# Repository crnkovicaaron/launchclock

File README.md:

# Rocket Launch Countdown Clock
A standalone digital countdown clock for rocket launches.
It displays countdown and mission elapsed time, is controlled entirely using a keypad, and requires no external computer or network.
It is built around an ATmega328P microcontroller, DS3231 real-time clock, and MAX7219-driven 7-segment and dot matrix displays.

## Features
- LED Displays: 7-segment for time and dot matrix for mode/status glyphs
- Fully keypad-driven UI
- Launch and current time/date setting (including launch date nudging)
- Countdown pausing
- Low-power sleep mode
- Display brightness control
- Configurable countdown time display format
- Error handling including invalid inputs and RTC power loss

## Hardware
Custom PCB designed in KiCad around an ATmega328P microcontroller.

Key components: 
- **MCU**: ATmega328P
- **RTC**: DS3231M with CR1220 battery backup
- **Displays**: MAX7219-driven dual 4-digit 7-segment (5641AS) and 8x8 dot matrix (1088AS)
- **Input**: 4x4 matrix keypad
- **Power**: 5V DC via 5.5x2.1mm barrel jack (or solder pads to enclosure-mounted barrel jack)
- **Communication**: I²C (RTC) and SPI (display drivers & ISP)
- **Assembly**: Hand soldered; uses both THD and SMD components
- **Enclosure**: Custom 3D printed FreeCAD enclosure is WIP

KiCad schematic and PCB files are under the 'hardware/' directory. Assorted photos can be found under the 'assets/' directory.

Status: Version 2 is completed and functional. Version 3 is WIP.

## Firmware
Written in Arduino C++ (AVR) for the ATmega328P (Arduino Uno).

The firmware implements a keypad-driven state machine that manages countdown/MET display, time/date setting, pause, brightness, sleep, and error handling.

Key elements:

- **Libraries**: RTClib (DS3231), Keypad, LedControl (MAX7219), EEPROM, plus AVR sleep/power utilities
- **Architecture**: Event-driven keypad handling and periodic 1-second time updates; use of mode flags for UI states
- **Displays**: Dual MAX7219 display control with PROGMEM bitmaps
- **Persistence**: Launch time/date stored in EEPROM
- **Power**: Full power-down sleep mode woken by keypad pin-change interrupt
- **Robustness**: Input validation, RTC power-loss detection, and dedicated error states

Source is a single sketch organized into functional blocks (display, input, timekeeping, power, UI modes). Programming is performed via the board's ISP header.

## Development History
### Initial Prototype
This Arduino breadboard prototype was an MVP with the singular goal of counting down to the Artemis II launch, with all work being completed entirely the day prior. It has the 7-segment displays wired directly to an Arduino Mega, uses a DS1307 RTC breakout board, and lacks any inputs.

### Revised Prototype
This revised prototype contains around a month of additions and improvements to the initial prototype. These include the addition of keypad inputs (out of frame), a dot matrix display, and corrected/improved display wiring. The vast majority of the time since the initial prototype was spent programming the firmware.

### Version 1 PCB
This custom 2-layer PCB mounts directly to an Arduino Mega using header pins, and the 7-segment displays mount to the board. With exception to the SMD resistors, there are essentially no changes to the circuit or its components between the revised prototype and the version 1 board. The main goal of this design was to become familiar with KiCad and PCB design.

### Version 2 PCB
The main goal of this version was to eliminate the Arduino and breakout boards by integrating all necessary functionality onto the board itself. This includes driving the 7-segment displays with a MAX7219 in the same manner as the dot matrix to allow the use of an MCU that is easier to solder by hand (instead of the ATmega2560 used on the Arduino Mega). The board is still 2-layers, programming is done via the ISP header, and numerous test points were integrated for troubleshooting and experimentation.

### Version 3 PCB (Work in Progress)
In this version, the barrel jack is superseded by a USB-C port with power and USB 2.0 data functionality. The MCU and display drivers use surface-mount packages in favor of through holes and most passive components are downsized to 0603 parts compared to the 1206 parts on version 2, allowing the total board area to be reduced by 28% compared to version 2. The board was designed to reduce EMI (mainly radiated), which includes switching to a 4-layer board. The revision also addresses numerous smaller issues with the version 2 board, including a soft but audible whine.

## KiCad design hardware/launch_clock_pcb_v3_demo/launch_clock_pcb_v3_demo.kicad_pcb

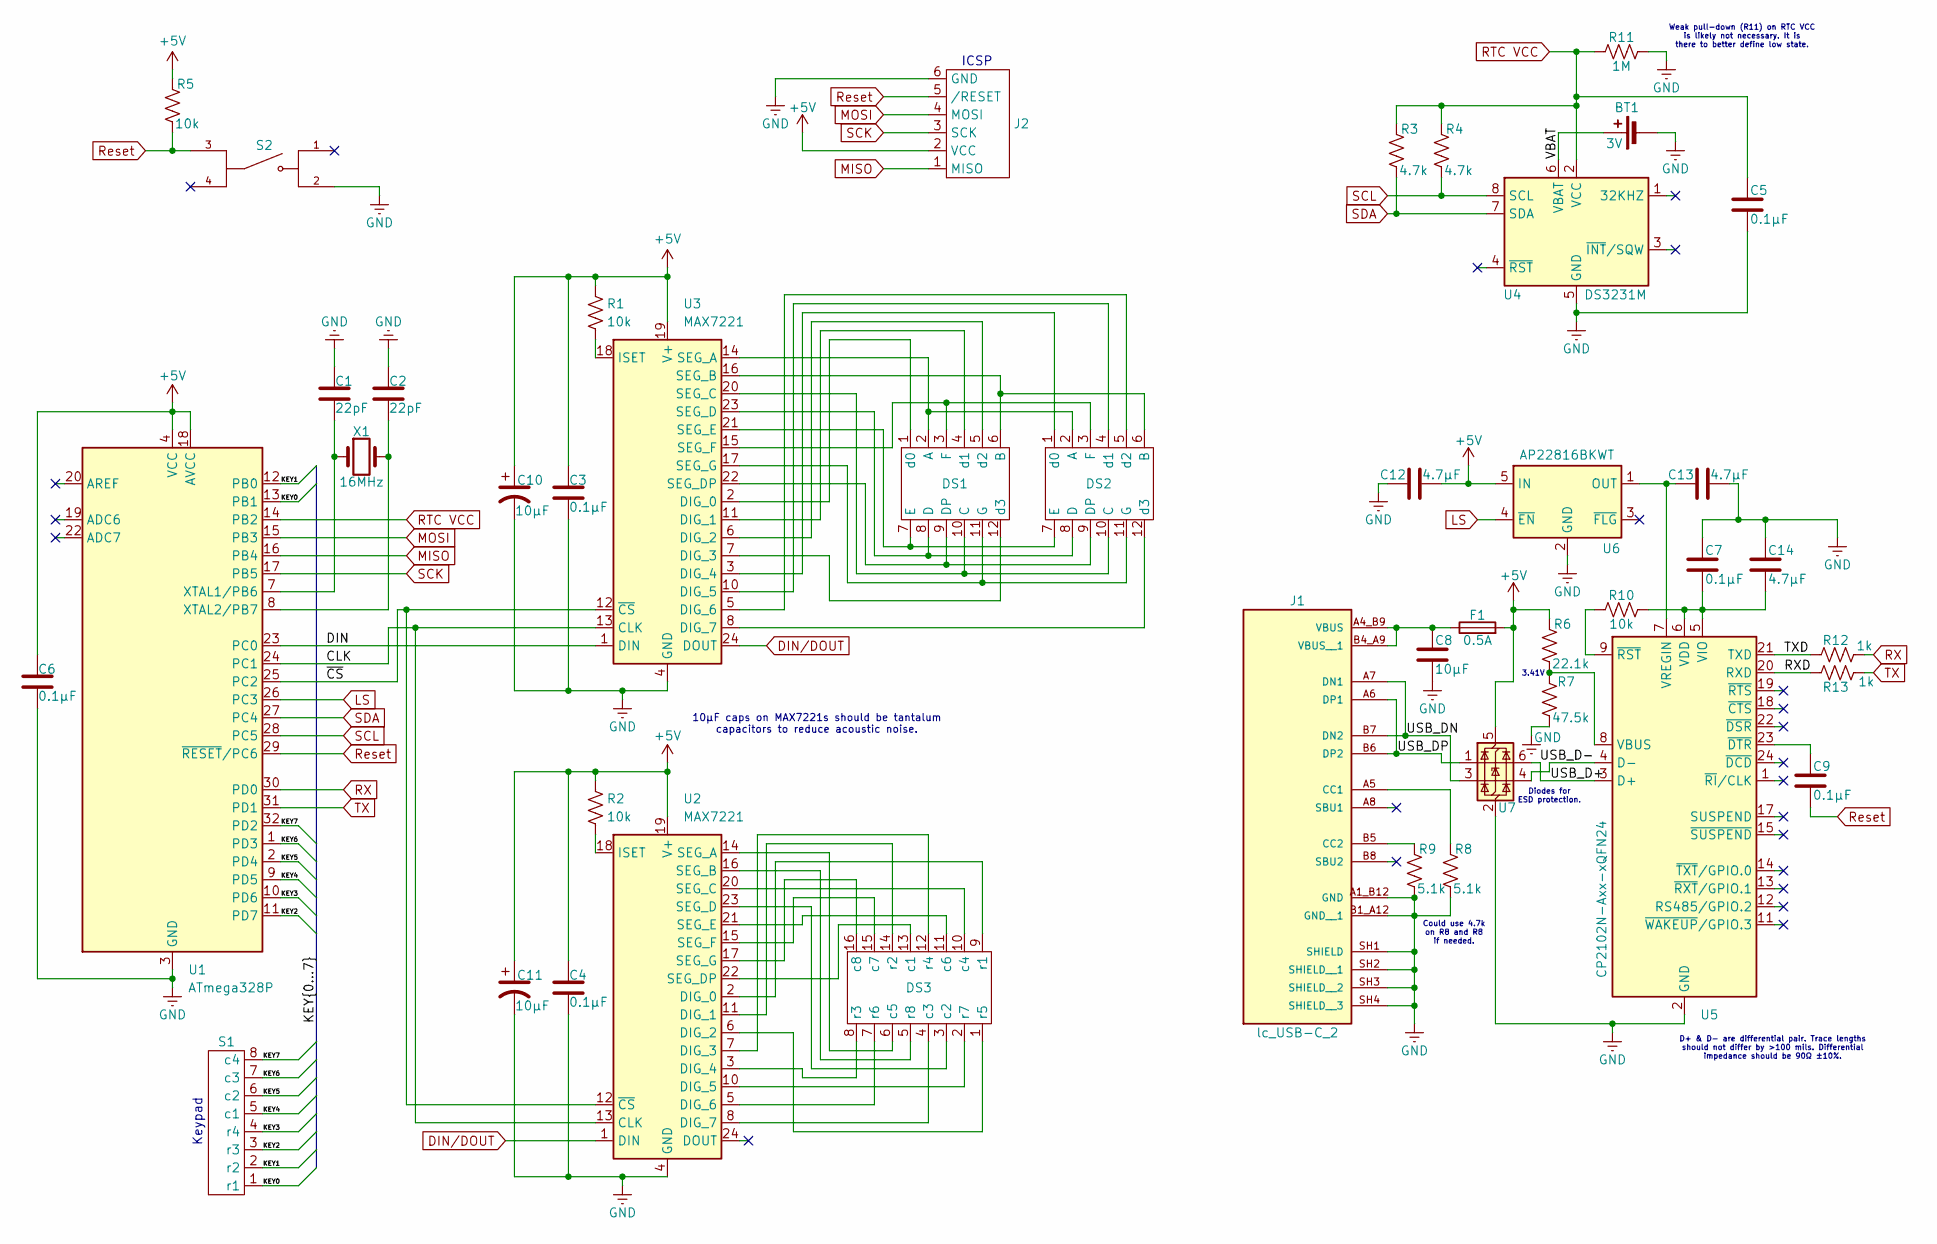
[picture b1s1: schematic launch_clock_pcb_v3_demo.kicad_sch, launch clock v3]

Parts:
BT1: 3V; BatteryHolder_Keystone_500
C1, C2: 22pF; C_0603_1608Metric_Pad1.08x0.95mm_HandSolder
C3, C4, C5, C6, C7, C9: 0.1µF; C_0603_1608Metric_Pad1.08x0.95mm_HandSolder
C8: 10µF; C_0603_1608Metric_Pad1.08x0.95mm_HandSolder
C10, C11: 10µF; lc_10µF_tantalum
C12, C13, C14: 4.7µF; C_0603_1608Metric_Pad1.08x0.95mm_HandSolder
DS1, DS2: launch_clock_7seg
DS3: 1088AS_footprint
F1: 0.5A; Fuse_1206_3216Metric_Pad1.42x1.75mm_HandSolder
J1: lc_USB-C_2; PARTREV 1.0
J2: PinHeader_2x03_P2.54mm_Vertical
R1, R2, R5, R10: 10k; R_0603_1608Metric_Pad0.98x0.95mm_HandSolder
R3, R4: 4.7k; R_0603_1608Metric_Pad0.98x0.95mm_HandSolder
R6: 22.1k; R_0603_1608Metric_Pad0.98x0.95mm_HandSolder
R7: 47.5k; R_0603_1608Metric_Pad0.98x0.95mm_HandSolder
R8, R9: 5.1k; R_0603_1608Metric_Pad0.98x0.95mm_HandSolder
R11: 1M; R_0603_1608Metric_Pad0.98x0.95mm_HandSolder
R12, R13: 1k; R_0603_1608Metric_Pad0.98x0.95mm_HandSolder
S1: PinHeader_1x08_P2.54mm_Horizontal
S2: lc_reset_button; PARTREV 1.02
U1: ATmega328P; TQFP-32_7x7mm_P0.8mm
U2, U3: MAX7221; SOIC-24W_7.5x15.4mm_P1.27mm
U4: DS3231M; SOIC-8_3.9x4.9mm_P1.27mm
U5: CP2102N-Axx-xQFN24; QFN-24-1EP_4x4mm_P0.5mm_EP2.6x2.6mm
U6: AP22816BKWT; SOT-23-5
U7: USBLC6-2SC6; SOT-23-6
X1: 16MHz; 16MHz_resonator

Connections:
+5V: C3.1, C4.1, C6.1, C10.1, C11.1, C12.2, F1.2, J2.2 (VCC), R1.1, R2.1, R5.1, R6.1, U1.4 (VCC), U1.6 (VCC), U1.18 (AVCC), U2.19 (V+), U3.19 (V+), U6.5 (IN), U7.5 (VBUS)
/CLK: U1.24 (PC1), U2.13 (CLK), U3.13 (CLK)
/DIN: U1.23 (PC0), U3.1 (DIN)
/KEY0: S1.1 (r1), U1.13 (PB1)
/KEY1: S1.2 (r2), U1.12 (PB0)
/KEY2: S1.3 (r3), U1.11 (PD7)
/KEY3: S1.4 (r4), U1.10 (PD6)
/KEY4: S1.5 (c1), U1.9 (PD5)
/KEY5: S1.6 (c2), U1.2 (PD4)
/KEY6: S1.7 (c3), U1.1 (PD3)
/KEY7: S1.8 (c4), U1.32 (PD2)
/RXD: R13.1, U5.20 (RXD)
/TXD: R12.1, U5.21 (TXD)
/USB_D+: U5.3 (D+), U7.6 (I/O1)
/USB_D-: U5.4 (D-), U7.4 (I/O2)
/USB_DN: J1.A7 (DN1), J1.B7 (DN2), U7.3 (I/O2)
/USB_DP: J1.A6 (DP1), J1.B6 (DP2), U7.1 (I/O1)
/VBAT: BT1.1 (+), U4.6 (VBAT)
/~CS: U1.25 (PC2), U2.12 (~CS), U3.12 (~CS)
DIN/DOUT: U2.1 (DIN), U3.24 (DOUT)
GND: BT1.2 (-), C1.1, C2.1, C3.2, C4.2, C5.2, C6.2, C7.1, C8.2, C10.2, C11.2, C12.1, C13.2, C14.1, J1.A1_B12 (GND), J1.B1_A12 (GND__1), J1.SH1 (SHIELD), J1.SH2 (SHIELD__1), J1.SH3 (SHIELD__2), J1.SH4 (SHIELD__3), J2.6 (GND), R7.2, R8.2, R9.2, R11.2, S2.2, U1.3 (GND), U1.5 (GND), U1.21 (GND), U2.4 (GND), U2.9 (GND), U3.4 (GND), U3.9 (GND), U4.5 (GND), U5.2 (GND), U5.25 (GND), U6.2 (GND), U7.2 (GND)
LS: U1.26 (PC3), U6.4 (~EN)
MISO: J2.1 (MISO), U1.16 (PB4)
MOSI: J2.4 (MOSI), U1.15 (PB3)
unnamed: DS1.2 (A), DS2.2 (A), U3.14 (SEG_A)
unnamed: DS1.6 (B), DS2.6 (B), U3.16 (SEG_B)
unnamed: DS1.10 (C), DS2.10 (C), U3.20 (SEG_C)
unnamed: DS1.8 (D), DS2.8 (D), U3.23 (SEG_D)
unnamed: DS1.9 (DP), DS2.9 (DP), U3.22 (SEG_DP)
unnamed: DS1.7 (E), DS2.7 (E), U3.21 (SEG_E)
unnamed: DS1.3 (F), DS2.3 (F), U3.15 (SEG_F)
unnamed: DS1.11 (G), DS2.11 (G), U3.17 (SEG_G)
unnamed: DS1.1 (d0), U3.2 (DIG_0)
unnamed: DS1.4 (d1), U3.11 (DIG_1)
unnamed: DS1.5 (d2), U3.6 (DIG_2)
unnamed: DS1.12 (d3), U3.7 (DIG_3)
unnamed: DS2.1 (d0), U3.3 (DIG_4)
unnamed: DS2.4 (d1), U3.10 (DIG_5)
unnamed: DS2.5 (d2), U3.5 (DIG_6)
unnamed: DS2.12 (d3), U3.8 (DIG_7)
unnamed: DS3.13 (c1), U2.22 (SEG_DP)
unnamed: DS3.3 (c2), U2.23 (SEG_D)
unnamed: DS3.4 (c3), U2.8 (DIG_7)
unnamed: DS3.10 (c4), U2.20 (SEG_C)
unnamed: DS3.6 (c5), U2.14 (SEG_A)
unnamed: DS3.11 (c6), U2.21 (SEG_E)
unnamed: DS3.15 (c7), U2.15 (SEG_F)
unnamed: DS3.16 (c8), U2.17 (SEG_G)
unnamed: DS3.9 (r1), U2.2 (DIG_0)
unnamed: DS3.14 (r2), U2.11 (DIG_1)
unnamed: DS3.8 (r3), U2.3 (DIG_4)
unnamed: DS3.12 (r4), U2.7 (DIG_3)
unnamed: DS3.1 (r5), U2.6 (DIG_2)
unnamed: DS3.7 (r6), U2.5 (DIG_6)
unnamed: DS3.2 (r7), U2.10 (DIG_5)
unnamed: DS3.5 (r8), U2.16 (SEG_B)
unnamed: J1.A5 (CC1), R8.1
unnamed: J1.B5 (CC2), R9.1
unnamed: C8.1, F1.1, J1.A4_B9 (VBUS), J1.B4_A9 (VBUS__1)
unnamed: C1.2, U1.7 (XTAL1/PB6), X1.1
unnamed: C2.2, U1.8 (XTAL2/PB7), X1.2
unnamed: R2.2, U2.18 (ISET)
unnamed: R1.2, U3.18 (ISET)
unnamed: R6.2, R7.1, U5.8 (VBUS)
unnamed: C7.2, C14.2, R10.2, U5.5 (VIO), U5.6 (VDD)
unnamed: C13.1, U5.7 (VREGIN), U6.1 (OUT)
unnamed: C9.1, U5.23 (~DTR)
unnamed: R10.1, U5.9 (~RST)
RTC VCC: C5.1, R3.1, R4.1, R11.1, U1.14 (PB2), U4.2 (VCC)
RX: R12.2, U1.30 (PD0)
Reset: C9.2, J2.5 (/RESET), R5.2, S2.3, U1.29 (~RESET/PC6)
SCK: J2.3 (SCK), U1.17 (PB5)
SCL: R4.2, U1.28 (PC5), U4.8 (SCL)
SDA: R3.2, U1.27 (PC4), U4.7 (SDA)
TX: R13.2, U1.31 (PD1)

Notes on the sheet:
D+ & D- are differential pair. Trace lengths should not differ by >100 mils. Differential impedance should be 90Ω ±10%.
ICSP
Weak pull-down (R11) on RTC VCC is likely not necessary. It is there to better define low state.
10µF caps on MAX7221s should be tantalum capacitors to reduce acoustic noise.
Keypad
Could use 4.7k on R8 and R8 if needed.
Diodes for ESD protection.
3.41V

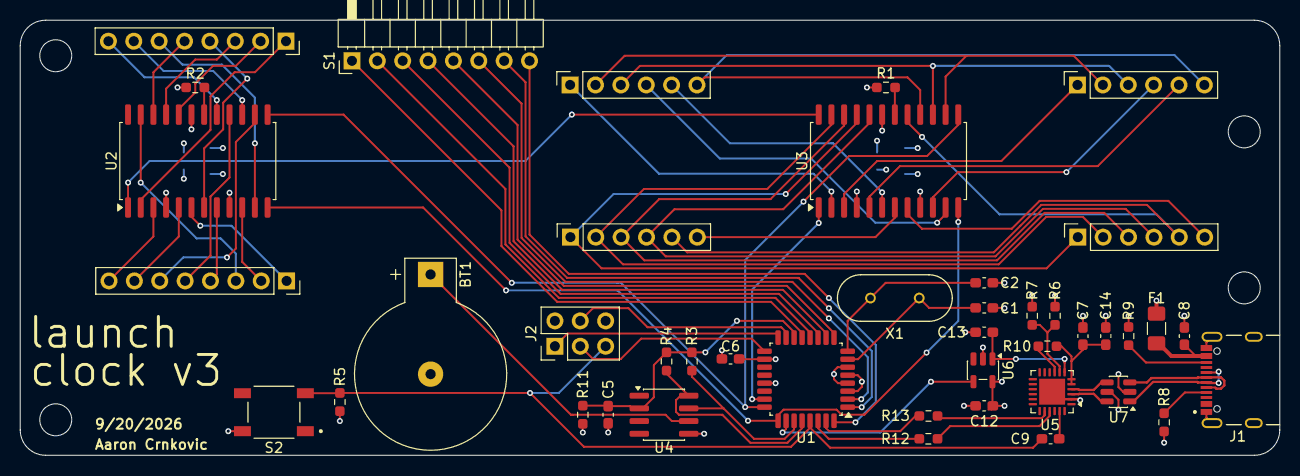
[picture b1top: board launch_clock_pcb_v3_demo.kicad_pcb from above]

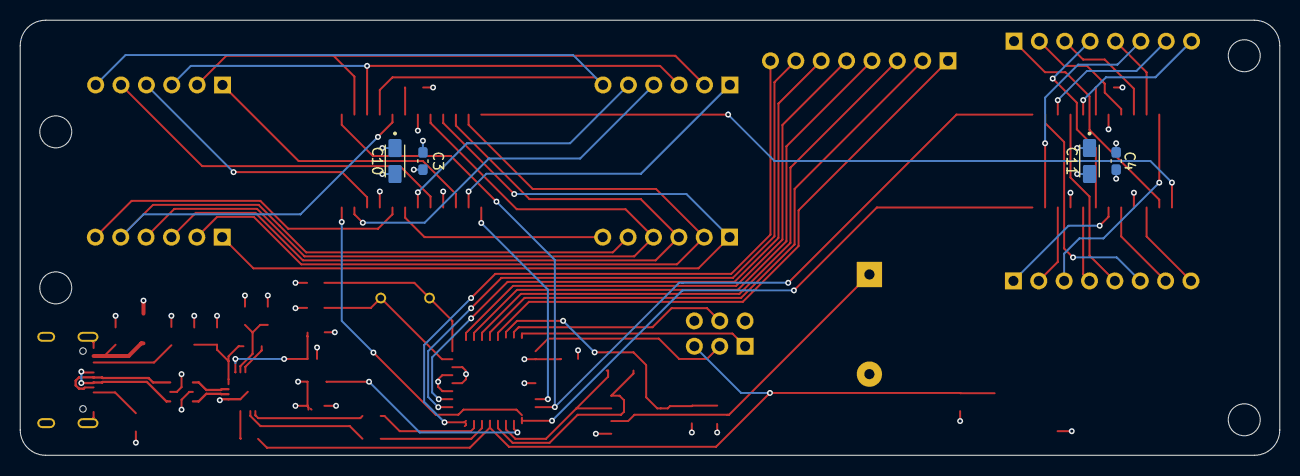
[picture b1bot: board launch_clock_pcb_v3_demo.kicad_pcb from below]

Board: 4 copper layers, 126.1 x 43.6 mm, 48 parts (4 on the bottom side), 75 nets.

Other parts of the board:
MT3, MT3#2, MT3#3, MT3#4: MountingHole_3.2mm_M3

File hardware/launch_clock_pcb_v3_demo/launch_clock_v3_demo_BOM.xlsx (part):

Reference | Qty | Value | Footprint | DKPN | Datasheet
BT1 | 1 | 3V | Battery:BatteryHolder_Keystone_500 | 36-500-ND | file:///C:/Users/Aaron%20Crnkovic/Downloads/500%20(1).PDF |  |  |  |  |  |  |  |  | EN | DKPN | Part | Board Qty | Order Qty | Part Cost | Part Tariff | Net Cost | Net Tariff | Tax | Total Cost | Board Cost |  |  | Sales Tax: | 7.4999999999999997E-2
C1,C2 | 2 | 22pF | Capacitor_SMD:C_0603_1608Metric_Pad1.08x0.95mm_HandSolder | 490-4942-1-ND | https://pim.murata.com/asset/pim4/ceramicCapacitorSMD/GCM188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 |  |  |  |  |  |  |  |  | 1 | 490-4942-1-ND | 22pF Ceramic Capacitor | 2 | 10 | 4.3999999999999997E-2 | 4.6299999999999996E-3 | 0.43999999999999995 | 4.6299999999999994E-2 | 3.6472499999999998E-2 | 0.48629999999999995 | 9.7259999999999985E-2
C3,C4,C5,C6,C7,C9 | 6 | 0.1µF | Capacitor_SMD:C_0603_1608Metric_Pad1.08x0.95mm_HandSolder | 490-14359-1-ND | https://pim.murata.com/asset/pim4/ceramicCapacitorSMD/GCM188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 |  |  |  |  |  |  |  |  | 1 | 490-14359-1-ND | 0.1µF Ceramic Capacitor | 6 | 20 | 8.2000000000000003E-2 | 8.7299999999999999E-3 | 1.6400000000000001 | 0.17460000000000001 | 0.13609500000000002 | 1.8146000000000002 | 0.54438000000000009
C8 | 1 | 10µF | Capacitor_SMD:C_0603_1608Metric_Pad1.08x0.95mm_HandSolder | 490-10475-1-ND | https://mm.digikey.com/Volume0/opasdata/d220001/medias/docus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 |  |  |  |  |  |  |  |  | 1 | 490-10475-1-ND | 10µF Ceramic Capacitor | 1 | 10 | 7.1999999999999995E-2 | 7.45E-3 | 0.72 | 7.4499999999999997E-2 | 5.9587499999999995E-2 | 0.79449999999999998 | 7.9449999999999993E-2
C10,C11 | 2 | 10µF | launch_clock_footprints:lc_10µF_tantalum | 478-11220-1-ND | https://datasheets.kyocera-avx.com/TAJ_AUTO.pdf |  |  |  |  |  |  |  |  | 1 | 478-11220-1-ND | 10µF Tantalum Capacitor | 2 | 10 | 0.31 | 2.4799999999999999E-2 | 3.1 | 0.248 | 0.25109999999999999 | 3.3479999999999999 | 0.66959999999999997
C12,C13,C14 | 3 | 4.7µF | Capacitor_SMD:C_0603_1608Metric_Pad1.08x0.95mm_HandSolder | 490-7203-1-ND | https://mm.digikey.com/Volume0/opasdata/d220001/medias/docus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 |  |  |  |  |  |  |  |  | 1 | 490-7203-1-ND | 4.7µF Ceramic Capacitor | 3 | 15 | 0.14099999999999999 | 1.469E-2 | 2.1149999999999998 | 0.22034999999999999 | 0.17515124999999995 | 2.3353499999999996 | 0.46706999999999987
DS1,DS2 | 2 | 1x6 female headers | launch_clock_footprints:launch_clock_7seg | 2223-SSK02-FPH-254-A6-ND | https://www.sameskydevices.com/product/resource/ssk02-fph-254.pdf |  |  |  |  |  |  |  |  | 1 | 2223-UJ20-C-H-G-SMT-1-P16-TRCT-ND | USB-C 2.0 Receptacle | 1 | 4 | 0.49 | 0.12862999999999999 | 1.96 | 0.51451999999999998 | 0.185589 | 2.4745200000000001 | 0.61863000000000001
DS3 | 1 | 1x8 female headers | launch_clock_footprints:1088AS_footprint | 2223-SSK02-FPH-254-A8-ND | https://www.sameskydevices.com/product/resource/ssk02-fph-254.pdf |  |  |  |  |  |  |  |  | 1 | 2223-TS18-5-25-SL-260-SMT-TRCT-ND | Push Button Switch (Reset) | 1 | 5 | 0.2 | 4.7469999999999998E-2 | 1 | 0.23735000000000001 | 9.2801249999999988E-2 | 1.2373499999999999 | 0.24747
F1 | 1 | 0.5A | Fuse:Fuse_1206_3216Metric_Pad1.42x1.75mm_HandSolder | 13-JB12F5000RCT-ND | https://mm.digikey.com/Volume0/opasdata/d220001/medias/docus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 |  |  |  |  |  |  |  |  | 1 | ATMEGA328PB-AU-ND | ATMEGA328PB | 1 | 4 | 1.63 | 0.12225 | 6.52 | 0.48899999999999999 | 0.52567499999999989 | 7.0089999999999995 | 1.7522499999999999
J1 | 1 | lc_USB-C_2 | launch_clock_footprints:lc_USB-C_2 | 2223-UJ20-C-H-G-SMT-1-P16-TRCT-ND | https://www.sameskydevices.com/product/resource/uj20-c-h-g-s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 |  |  |  |  |  |  |  |  | 1 | 175-DS3231MZ+TRLCT-ND | DS3231MZ [8 pin] | 1 | 2 | 13.85 | 1.1080000000000001 | 27.7 | 2.2160000000000002 | 2.2437 | 29.916 | 14.958
J2 | 1 | ICSP | Connector_PinHeader_2.54mm:PinHeader_2x03_P2.54mm_Vertical |  |  |  |  |  |  |  |  |  |  | 1 | 336-5887-ND | CP2102N [24 pin] | 1 | 3 | 5.15 | 2.06 | 15.450000000000001 | 6.18 | 1.6222500000000002 | 21.630000000000003 | 7.2100000000000009
R1,R2,R5,R10 | 4 | 10k | Resistor_SMD:R_0603_1608Metric_Pad0.98x0.95mm_HandSolder |  |  |  |  |  |  |  |  |  |  | 1 | 31-AP22816BKWT-7CT-ND | AP22816B (load switch) | 1 | 5 | 0.31 | 0.11625000000000001 | 1.55 | 0.58125000000000004 | 0.15984375000000001 | 2.1312500000000001 | 0.42625000000000002
R3,R4 | 2 | 4.7k | Resistor_SMD:R_0603_1608Metric_Pad0.98x0.95mm_HandSolder |  |  |  |  | Height | Width | Area |  |  |  | 1 | 497-5235-1-ND | USBLC6 (ESD diodes) | 1 | 4 | 0.54 | 0.24299999999999999 | 2.16 | 0.97199999999999998 | 0.2349 | 3.1320000000000001 | 0.78300000000000003
R6 | 1 | 22.1k | Resistor_SMD:R_0603_1608Metric_Pad0.98x0.95mm_HandSolder |  |  |  | V2: | 2.1 | 5.5 | 11.55 |  |  |  | 1 | 36-500-ND | Battery Holder [CR1220] | 1 | 3 | 1.3 | 0 | 3.9000000000000004 | 0 | 0.29250000000000004 | 3.9000000000000004 | 1.3
R7 | 1 | 47.5k | Resistor_SMD:R_0603_1608Metric_Pad0.98x0.95mm_HandSolder |  |  |  | V3: | 1.6759999999999999 | 4.9649999999999999 | 8.3213399999999993 |  |  |  | 1 | 2223-SSK02-FPH-254-A6-ND | 1x6 2.54mm [Str-F] (7-seg) | 4 | 10 | 0.30599999999999999 | 8.5680000000000006E-2 | 3.06 | 0.85680000000000001 | 0.29376000000000002 | 3.9168000000000003 | 1.5667200000000001
R8,R9 | 2 | 5.1k | Resistor_SMD:R_0603_1608Metric_Pad0.98x0.95mm_HandSolder | P5.10KHCT-ND | https://industrial.panasonic.com/cdbs/www-data/pdf/RDA0000/A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 |  |  |  |  | 0.72046233766233758 |  |  |  | 1 | 2223-SSK02-FPH-254-A8-ND | 1x8 2.54mm [Str-F] (Mtrx) | 2 | 4 | 0.4 | 0.112 | 1.6 | 0.44800000000000001 | 0.15359999999999999 | 2.048 | 1.024
R11 | 1 | 1M | Resistor_SMD:R_0603_1608Metric_Pad0.98x0.95mm_HandSolder |  |  |  |  |  |  |  |  |  |  | 1 | P5.10KHCT-ND | 5.1kΩ Resistor [0603] | 2 | 10 | 3.9E-2 | 1.0240000000000001E-2 | 0.39 | 0.1024 | 3.6929999999999998E-2 | 0.4924 | 9.8479999999999998E-2
R12,R13 | 2 | 1k | Resistor_SMD:R_0603_1608Metric_Pad0.98x0.95mm_HandSolder |  |  |  |  |  |  |  |  |  |  | 1 | 1528-3844-ND | 4x4 Keypad | 1 | 1 | 5.95 | 0 | 5.95 | 0 | 0.44624999999999998 | 5.95 | 5.95
S1 | 1 | keypad | Connector_PinHeader_2.54mm:PinHeader_1x08_P2.54mm_Horizontal |  |  |  |  |  |  |  |  |  |  |  |  |  |  |  |  |  | 79.25500000000001 | 13.36107 | 6.9462052500000002 | 104.55227525000001 | 44.73876525
S2 | 1 | lc_reset_button | launch_clock_footprints:lc_reset_button | 2223-TS18-5-25-SL-260-SMT-TRCT-ND | https://www.sameskydevices.com/product/resource/ts18.pdf |  |  |  |  |  |  |  |  | 1 | amazon_MAX7221_option1 | MAX7221 [10pcs] | 2 | 10 | 0.95499999999999996 | 0 | 9.5499999999999989 | 0 | 0.71624999999999994 | 10.266249999999999 | 2.0532499999999998
U1 | 1 | ATmega328P | Package_QFP:TQFP-32_7x7mm_P0.8mm | ATMEGA328PB-AU-ND | https://ww1.microchip.com/downloads/en/DeviceDoc/40001907A.pdf |  |  |  |  |  |  |  |  | 0 | amazon_MAX7221_option2 | MAX7221 [5pcs] | 2 | 5 | 1.506 | 0 | 7.53 | 0 | 0.56474999999999997 | 8.0947499999999994 | 3.2378999999999998
U2,U3 | 2 | MAX7221 | Package_SO:SOIC-24W_7.5x15.4mm_P1.27mm | N/A | https://datasheets.maximintegrated.com/en/ds/MAX7219-MAX7221.pdf |  |  |  |  |  |  |  |  | 0 | amazon_MAX7221_option3 | MAX7221 [5pcs] | 2 | 5 | 1.714 | 0 | 8.57 | 0 | 0.64275000000000004 | 9.2127499999999998 | 3.6850999999999998
U4 | 1 | DS3231M | Package_SO:SOIC-8_3.9x4.9mm_P1.27mm | 175-DS3231MZ+TRLCT-ND | http://datasheets.maximintegrated.com/en/ds/DS3231M.pdf |  |  |  |  |  |  |  |  | 1 | PCBWay | launch_clock_pcb_v3 [5pcs] | 1 | 5 | 13.524000000000001 | (unkn) | 67.62 | (unkn) | 5.0715000000000003 | 85.385300000000015 | 17.077060000000003
U5 | 1 | CP2102N-Axx-xQFN24 | Package_DFN_QFN:QFN-24-1EP_4x4mm_P0.5mm_EP2.6x2.6mm | 336-5887-ND | https://www.silabs.com/documents/public/data-sheets/cp2102n-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 |  |  |  |  |  |  |  |  | 0 | OSHPark | launch_clock_pcb_v3 [3pcs] | 1 | 3 | 28.400000000000002 | 0 | 85.2 | 0 | 6.39 | 91.59 | 30.53
U6 | 1 | AP22816BKWT | Package_TO_SOT_SMD:SOT-23-5 | 31-AP22816BKWT-7CT-ND | https://www.diodes.com/assets/Datasheets/AP22816_17_18.pdf |  |  |  |  |  |  |  |  |  |  |  |  |  |  |  |  |  |  | 200.20382525000002 | 63.869075250000002
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
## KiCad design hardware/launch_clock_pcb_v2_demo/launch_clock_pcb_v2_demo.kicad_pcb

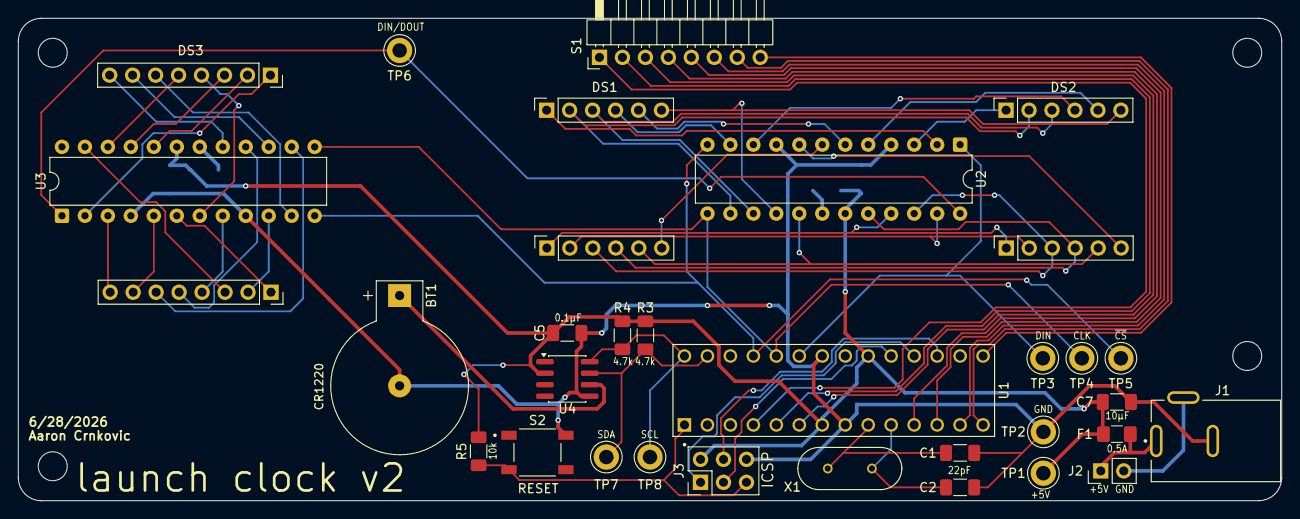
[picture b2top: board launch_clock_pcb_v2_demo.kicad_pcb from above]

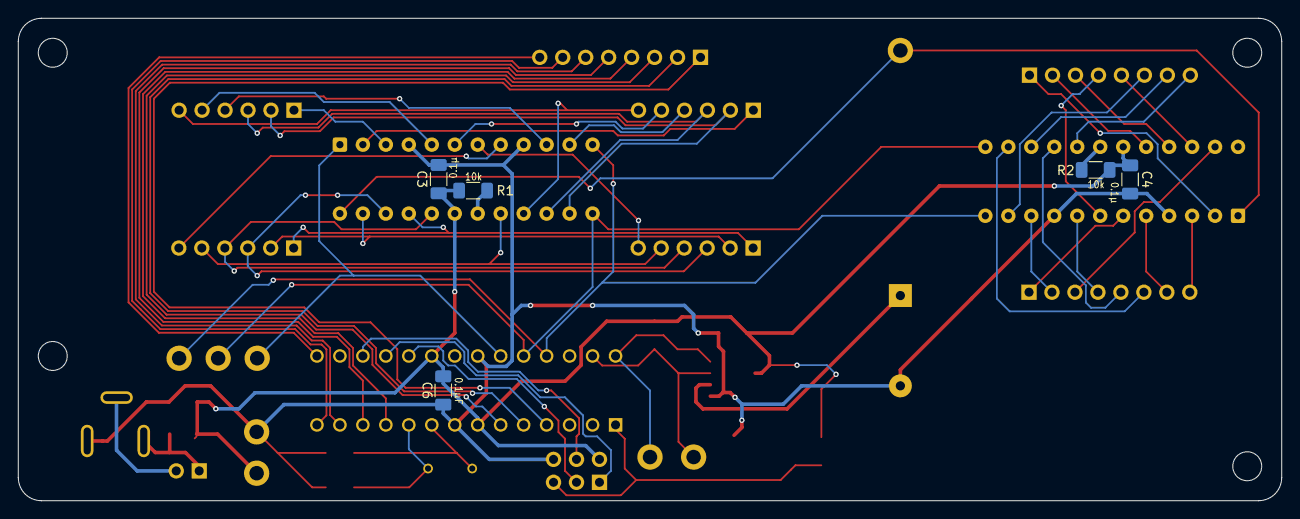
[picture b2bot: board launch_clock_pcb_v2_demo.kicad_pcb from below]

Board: 2 copper layers, 139.7 x 53.3 mm, 38 parts (5 on the bottom side), 59 nets.

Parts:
BT1: 3V; BatteryHolder_Keystone_500
C1, C2: 22pF; C_1206_3216Metric_Pad1.33x1.80mm_HandSolder
C3, C4, C5, C6: 0.1µF; C_1206_3216Metric_Pad1.33x1.80mm_HandSolder
C7: 10µF; C_1206_3216Metric_Pad1.33x1.80mm_HandSolder
DS1, DS2: launch_clock_7seg
DS3: 1088AS_footprint
F1: 0.5A; Fuse_1206_3216Metric_Pad1.42x1.75mm_HandSolder
J1: 5V Barrel Jack; 5.5x2.1mm_barrel_jack
J2: External 5V Source; PinHeader_1x02_P2.54mm_Vertical
J3: PinHeader_2x03_P2.54mm_Vertical
MT1, MT3, MT4: MountingHole_3.2mm_M3
R1, R2, R5: 10k; R_1206_3216Metric_Pad1.30x1.75mm_HandSolder
R3, R4: 4.7k; R_1206_3216Metric_Pad1.30x1.75mm_HandSolder
S1: PinHeader_1x08_P2.54mm_Horizontal
S2: SW_TS18-5-25-SL-260-SMT-TR; lc_reset_button
TP1, TP2, TP3, TP4, TP5, TP6, TP7, TP8: TestPoint_Small; TestPoint_Keystone_5005-5009_Compact
U1: ATmega328-P; lc_mcu_carriage
U2, U3: MAX7221xNG; DIP-24_W7.62mm
U4: DS3231MZ; SOIC-8_3.9x4.9mm_P1.27mm
X1: 16MHz; 16MHz_resonator

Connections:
+5V: C3.1, C4.1, C5.1, C6.1, C7.1, F1.2, J3.2 (VCC), R1.1, R2.1, R3.1, R4.1, R5.1, TP1.1 (1_1), U1.7 (VCC), U1.20 (AVCC), U2.19 (V+), U3.19 (V+), U4.2 (VCC)
/KEY0: S1.1 (r1), U1.4 (PD2)
/KEY1: S1.2 (r2), U1.5 (PD3)
/KEY2: S1.3 (r3), U1.6 (PD4)
/KEY3: S1.4 (r4), U1.11 (PD5)
/KEY4: S1.5 (c1), U1.12 (PD6)
/KEY5: S1.6 (c2), U1.13 (PD7)
/KEY6: S1.7 (c3), U1.14 (PB0)
/KEY7: S1.8 (c4), U1.15 (PB1)
DIN/DOUT: TP6.1 (1_1), U2.24 (DOUT), U3.1 (DIN)
GND: BT1.2 (-), C1.1, C2.1, C3.2, C4.2, C5.2, C6.2, C7.2, J1.B, J3.6 (GND), S2.2, TP2.1 (1_1), U1.8 (GND), U1.22 (GND), U2.4 (GND), U2.9 (GND), U3.4 (GND), U3.9 (GND), U4.5 (GND)
MISO: J3.1 (MISO), U1.18 (PB4)
MOSI: J3.4 (MOSI), U1.17 (PB3)
unnamed: BT1.1 (+), U4.6 (VBAT)
unnamed: DS1.2 (A), DS2.2 (A), U2.14 (SEG_A)
unnamed: DS1.6 (B), DS2.6 (B), U2.16 (SEG_B)
unnamed: DS1.10 (C), DS2.10 (C), U2.20 (SEG_C)
unnamed: DS1.8 (D), DS2.8 (D), U2.23 (SEG_D)
unnamed: DS1.9 (DP), DS2.9 (DP), U2.22 (SEG_DP)
unnamed: DS1.7 (E), DS2.7 (E), U2.21 (SEG_E)
unnamed: DS1.3 (F), DS2.3 (F), U2.15 (SEG_F)
unnamed: DS1.11 (G), DS2.11 (G), U2.17 (SEG_G)
unnamed: DS1.1 (d0), U2.2 (DIG_0)
unnamed: DS1.4 (d1), U2.11 (DIG_1)
unnamed: DS1.5 (d2), U2.6 (DIG_2)
unnamed: DS1.12 (d3), U2.7 (DIG_3)
unnamed: DS2.1 (d0), U2.3 (DIG_4)
unnamed: DS2.4 (d1), U2.10 (DIG_5)
unnamed: DS2.5 (d2), U2.5 (DIG_6)
unnamed: DS2.12 (d3), U2.8 (DIG_7)
unnamed: DS3.13 (c1), U3.22 (SEG_DP)
unnamed: DS3.3 (c2), U3.23 (SEG_D)
unnamed: DS3.4 (c3), U3.8 (DIG_7)
unnamed: DS3.10 (c4), U3.20 (SEG_C)
unnamed: DS3.6 (c5), U3.14 (SEG_A)
unnamed: DS3.11 (c6), U3.21 (SEG_E)
unnamed: DS3.15 (c7), U3.15 (SEG_F)
unnamed: DS3.16 (c8), U3.17 (SEG_G)
unnamed: DS3.9 (r1), U3.2 (DIG_0)
unnamed: DS3.14 (r2), U3.11 (DIG_1)
unnamed: DS3.8 (r3), U3.3 (DIG_4)
unnamed: DS3.12 (r4), U3.7 (DIG_3)
unnamed: DS3.1 (r5), U3.6 (DIG_2)
unnamed: DS3.7 (r6), U3.5 (DIG_6)
unnamed: DS3.2 (r7), U3.10 (DIG_5)
unnamed: DS3.5 (r8), U3.16 (SEG_B)
unnamed: F1.1, J1.A, J2.1
unnamed: J1.C, J2.2
unnamed: TP3.1 (1_1), U1.23 (PC0), U2.1 (DIN)
unnamed: TP4.1 (1_1), U1.24 (PC1), U2.13 (CLK), U3.13 (CLK)
unnamed: TP5.1 (1_1), U1.25 (PC2), U2.12 (~CS), U3.12 (~CS)
unnamed: C1.2, U1.9 (XTAL1/PB6), X1.1
unnamed: C2.2, U1.10 (XTAL2/PB7), X1.2
unnamed: R1.2, U2.18 (ISET)
unnamed: R2.2, U3.18 (ISET)
Reset: J3.5 (/RESET), R5.2, S2.3, U1.1 (~RESET/PC6)
SCK: J3.3 (SCK), U1.19 (PB5)
SCL: R4.2, TP8.1 (1_1), U1.28 (PC5), U4.8 (SCL)
SDA: R3.2, TP7.1 (1_1), U1.27 (PC4), U4.7 (SDA)

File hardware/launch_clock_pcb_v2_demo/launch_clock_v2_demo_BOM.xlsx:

| Reference | Qty | Value | Datasheet | DKPN | Link
Battery Holder | BT1 | 1 | 3V | file:///C:/Users/Aaron%20Crnkovic/Downloads/500%20(1).PDF | 36-500-ND
 | C1,C2 | 2 | 22pF
 | C3,C4,C5,C6 | 4 | 0.1µF
10uF capacitors | C7 | 1 | 10µF | https://yageogroup.com/content/datasheet/asset/file/UPY-GPHC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 | 311-2007-1-ND
5641AS display | DS1,DS2 | 2 |  |  |  | https://handsontec.com/index.php/product/0-56-4-digit-with-d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
1088AS display | DS3 | 1 |  |  |  | https://handsontec.com/index.php/product/3mm-8x8-dot-matrix-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
0.5A fuse | F1 | 1 | 0.5A | https://mm.digikey.com/Volume0/opasdata/d220001/medias/docus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 | 13-JB12F5000RCT-ND
5V Barrel Jack | J1 | 1 |  | https://tensility.s3.us-west-2.amazonaws.com/uploads/pdffile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 | 839-54-00166-ND
External 5V Source | J2 | 1 | External 5V Source
 | J3 | 1
 | R1,R2,R5 | 3 | 10k
 | R3,R4 | 2 | 4.7k
Keypad | S1 | 1 |  | https://mm.digikey.com/Volume0/opasdata/d220001/medias/docus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 | 1528-3844-ND
Reset button | S2 | 1 | lc_reset_button | https://www.sameskydevices.com/product/resource/ts18.pdf | 2223-TS18-5-25-SL-260-SMT-TRCT-ND
Test points | TP1,TP2,TP3,TP4,TP5,TP6,TP7,TP8 | 8 | TestPoint_Small | https://www.keyelco.com/userAssets/file/K75p62.pdf | 36-5005-ND
 | U1 | 1 | ATmega328-P | https://ww1.microchip.com/downloads/en/DeviceDoc/ATmega48A-P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 | ATMEGA328P-PU-ND
 | U2,U3 | 2 | MAX7221xNG | https://datasheets.maximintegrated.com/en/ds/MAX7219-MAX7221.pdf |  | https://www.amazon.com/Bridgold-MAX7219CNG-MAX7219-Serially-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
 | U4 | 1 | DS3231MZ | http://datasheets.maximintegrated.com/en/ds/DS3231M.pdf | 175-DS3231MZ+TRLCT-ND
 | X1 | 1 | 16MHz | https://cfd.citizen.co.jp/cms/cfd/pdf/english/HC-49_U-S_E.pdf | 300-6034-ND | https://www.amazon.com/uxcell-Crystal-Oscillators-Resonators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
1x8 female headers |  | 2 |  |  | 2223-SSK02-FPH-254-A8-ND
MCU carriage |  | 1 |  | https://www.on-shore.com/wp-content/uploads/2015/09/ipg2.pdf | ED3050-5-ND

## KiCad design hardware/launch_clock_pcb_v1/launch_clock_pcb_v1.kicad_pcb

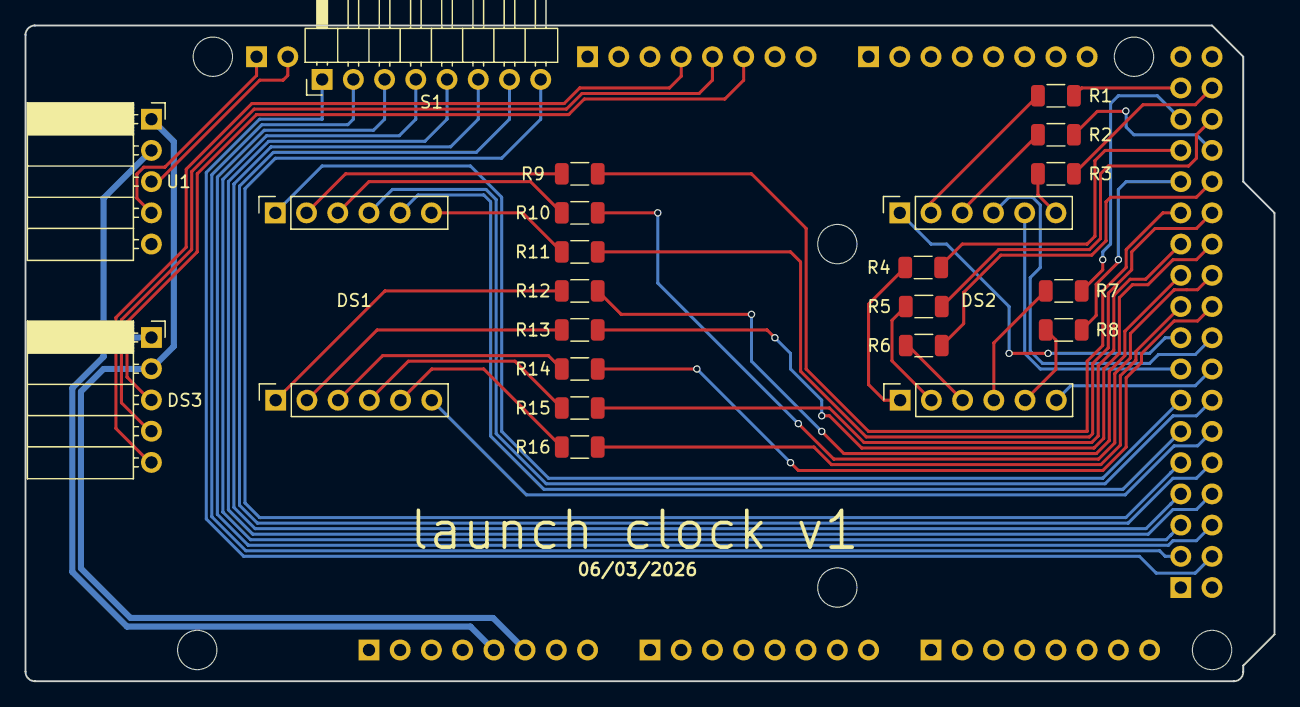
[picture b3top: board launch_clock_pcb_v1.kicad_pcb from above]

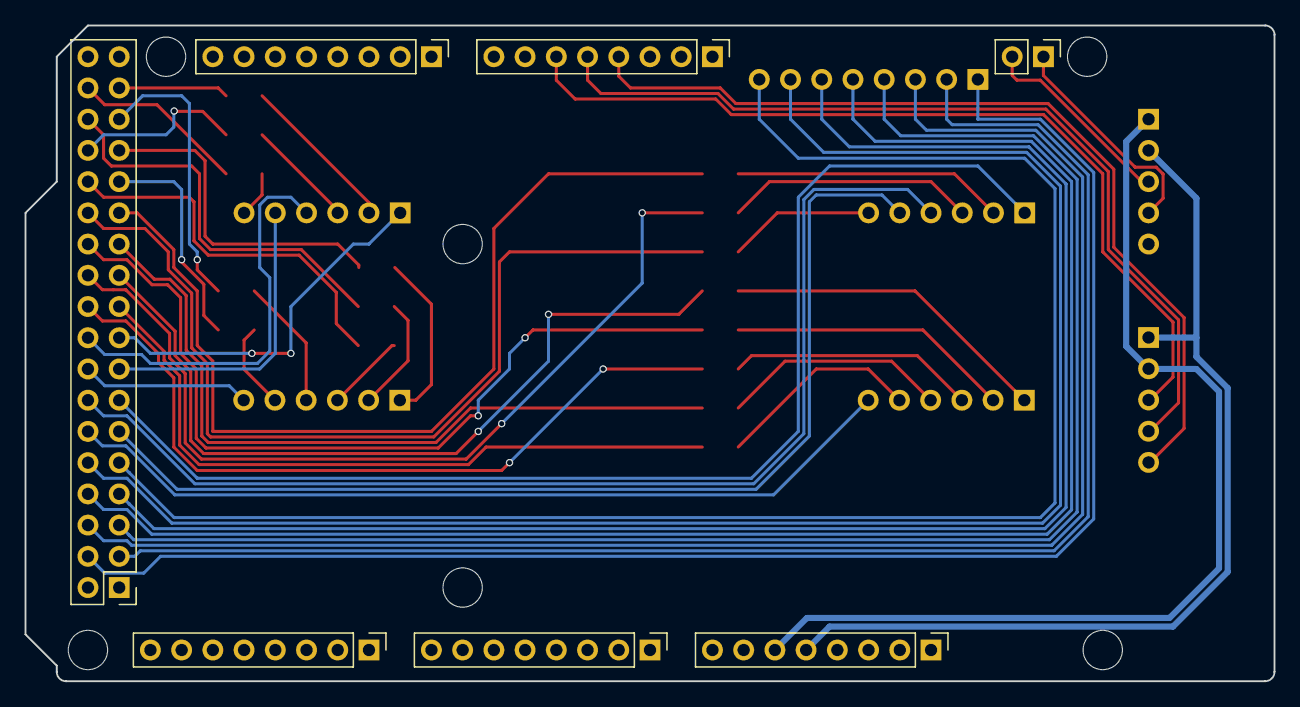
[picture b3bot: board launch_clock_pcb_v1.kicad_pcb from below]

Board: 2 copper layers, 101.6 x 53.3 mm, 34 parts (7 on the bottom side), 55 nets.

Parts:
DS1, DS2: launch_clock_7seg
DS3: PinSocket_1x05_P2.54mm_Horizontal
J1: Power; PinHeader_1x08_P2.54mm_Vertical
J2: PWM; PinHeader_1x02_P2.54mm_Vertical
J3, J5: Analog; PinHeader_1x08_P2.54mm_Vertical
J4: PWM; PinHeader_1x08_P2.54mm_Vertical
J6: Communication; PinHeader_1x08_P2.54mm_Vertical
J7: Digital; PinHeader_2x18_P2.54mm_Vertical
MH1, MH2, MH3, MH4, MH5, MH6: MountingHole_3.2mm
R1, R2, R3, R4, R5, R6, R7, R8, R9, R10, R11, R12, R13, R14, R15, R16: 220; R_1206_3216Metric
S1: PinHeader_1x08_P2.54mm_Horizontal
U1: PinSocket_1x05_P2.54mm_Horizontal

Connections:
+5V: DS3.1 (VCC), J1.5, J7.35, J7.36, U1.2 (VCC)
/22: J7.33, R1.1
/23: J7.34, R3.1
/24: J7.31, R7.2
/25: J7.32, R5.2
/26: J7.29, R4.2
/27: J7.30, R2.1
/28: J7.27, R8.2
/29: J7.28, R6.2
/30: J7.25, R9.1
/31: J7.26, R11.1
/32: J7.23, R15.2
/33: J7.24, R13.2
/34: J7.21, R12.2
/35: J7.22, R10.1
/36: J7.19, R16.2
/37: J7.20, R14.2
/38: DS2.1 (d0), J7.17
/39: DS2.4 (d1), J7.18
/40: DS2.5 (d2), J7.15
/41: DS2.12 (d3), J7.16
/42: DS1.1 (d0), J7.13
/43: DS1.4 (d1), J7.14
/47: J7.10, S1.7 (c3)
/48: J7.7, S1.6 (c2)
/49: J7.8, S1.5 (c1)
/50: J7.5, S1.4 (r4)
/51: J7.6, S1.3 (r3)
/53: J7.4, S1.1 (r1)
/*2: DS3.3 (DIN), J4.6
/*3: DS3.4 (CS), J4.5
/*4: DS3.5 (CLK), J4.4
/*44: DS1.5 (d2), J7.11
/*45: DS1.12 (d3), J7.12
/*46: J7.9, S1.8 (c4)
/*52: J7.3, S1.2 (r2)
/SCL/21: J2.1, J6.8, U1.4 (SCL)
/SDA/20: J2.2, J6.7, U1.3 (SDA)
GND: DS3.2 (GND), J1.6, J1.7, J7.1, J7.2, U1.1 (GND)
unnamed: DS1.2 (A), R9.2
unnamed: DS1.6 (B), R11.2
unnamed: DS1.10 (C), R15.1
unnamed: DS1.8 (D), R13.1
unnamed: DS1.9 (DP), R14.1
unnamed: DS1.7 (E), R12.1
unnamed: DS1.3 (F), R10.2
unnamed: DS1.11 (G), R16.1
unnamed: DS2.2 (A), R1.2
unnamed: DS2.6 (B), R3.2
unnamed: DS2.10 (C), R7.1
unnamed: DS2.8 (D), R5.1
unnamed: DS2.9 (DP), R6.1
unnamed: DS2.7 (E), R4.1
unnamed: DS2.3 (F), R2.2
unnamed: DS2.11 (G), R8.1
